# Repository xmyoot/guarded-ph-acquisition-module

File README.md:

# Guarded pH Acquisition Module

**Rev A · engineering prototype · CAD reviewed 21 October 2026 · unbuilt / hardware validation pending**

A 50 × 35 mm, two-layer pH analog front end for an external ESP32-S3 host. The design combines an LMP91200 electrode buffer, ADS112C04 16-bit delta-sigma ADC, REF3220 2.048 V reference, and a quiet 3.3 V supply with delayed reference enable.

*CAD rendering, not a photograph. The BNC connector is a drawing-derived visualization with threaded barrel, bayonet lugs and socket; small details are approximate, not vendor mechanical CAD.*

## Engineering focus

- Driven guards on both faces surround a 4.143 mm top-layer electrode trace with no vias or test-point stubs.
- Differential conversion at gain 2, external 2.048 V reference, and nominal 20 SPS single-shot mode; 31.25 µV per code. This is resolution, **not demonstrated accuracy**.
- Matched 1 kΩ input resistors and a 10 nF C0G differential capacitor; calculated pole 7.96 kHz.
- Supervisor-controlled reference startup, local test access, removable I²C pullups, and diagnostic/calibration firmware.
- Frozen project symbols and footprints; complete Gerber, drill, placement, and BOM outputs.
- Route cleanup reduced track segments from 352 to 257 and removed 8.203 mm of unnecessary copper while preserving locked analog geometry.

## Review status

Native KiCad 10.0.7 reports **0 ERC errors/warnings, 0 DRC violations, 0 unconnected pads, and 0 schematic-parity footprint errors**. A separate audit matches every native pad net and checks input geometry, copper exclusion, and via/paste separation. Generic analyzer findings and deliberate rule exceptions are explained in the [design review](docs/implementation/design_review.md).

The board has not been fabricated, assembled, powered, or tested. Leakage, noise, settling, startup, effective capacitor values, probe calibration, and interference remain hardware acceptance tests. The ≤0.01 pH electronics objective is an unproven target. There is no field ESD protection, onboard isolation, motor driver, battery system, radio, or cloud application.

## Files

| Deliverable | Location |
|---|---|
| Native KiCad project | [Soil_pH_AFE.kicad_pro](hardware/Soil_pH_AFE/Soil_pH_AFE.kicad_pro) |
| Schematic PDF | [schematic.pdf](output/review/schematic.pdf) |
| Fabrication package | [Rev A Gerber/drill ZIP](output/Soil_pH_AFE_RevA_fabrication.zip) |
| Fabrication and assembly instructions | [fabrication_notes.md](docs/implementation/fabrication_notes.md) |
| Orderable board BOM / host mating parts | [BOM.csv](output/assembly/BOM.csv) / [mating_parts.csv](output/assembly/mating_parts.csv) |
| Assembly drawing / placement | [assembly_top.pdf](output/assembly/assembly_top.pdf) / [placement_smd.csv](output/assembly/placement_smd.csv) |
| Firmware / bring-up | [Arduino sketch](firmware/SoilPH_Bringup/SoilPH_Bringup.ino) / [bringup.md](docs/implementation/bringup.md) |
| Review and decisions | [design_review.md](docs/implementation/design_review.md) / [decisions.md](docs/implementation/decisions.md) |
| Architecture and calculations | [Architecture](docs/architecture/01_architecture.md) / [calculations.json](docs/architecture/calculations.json) |
| Release hashes | [SHA256SUMS.txt](output/SHA256SUMS.txt) |
| Tools and reproducibility | [tools.md](docs/implementation/tools.md) |

## Scope and integration

This is an independent bench prototype based on an incomplete soil-instrument brief. Original Altium files and the promised replacement schematic were unavailable. The design therefore implements the requested analog chain on a separate board; it does not claim to preserve or reproduce the original product. Original client screenshots are retained locally and excluded from the public repository; the architecture contains the technical requirement summary.

Supply J2 with regulated 4.75–5.25 V and use 3.3 V open-drain I²C. J2: **1 = +5 V, 2 = ground, 3 = SDA, 4 = SCL, 5 = ground, 6 = reserved/unconnected**. Confirm pin 1 on the assembly drawing; do not infer it from viewing the cable end.

The insulated BNC shell is driven at approximately 1.024 V (`PH_VCM`); **it is not ground**. Use only a floating sample with no other conductive connection. Product integration requires a separately qualified isolated power and I²C interface, plus connector protection with a measured leakage budget. See [bring-up](docs/implementation/bringup.md) before applying power.

Phase 1 documents are retained as historical planning; final implementation decisions and BOM take precedence. Design/review used [kicad-happy](https://github.com/aklofas/kicad-happy) and routing used [KiCadRoutingTools](https://github.com/drandyhaas/KiCadRoutingTools), with manual protection of the high-impedance input and guard. Architecture was developed with Astra and implementation with 6.1 Sol; automated checks do not replace physical engineering qualification.

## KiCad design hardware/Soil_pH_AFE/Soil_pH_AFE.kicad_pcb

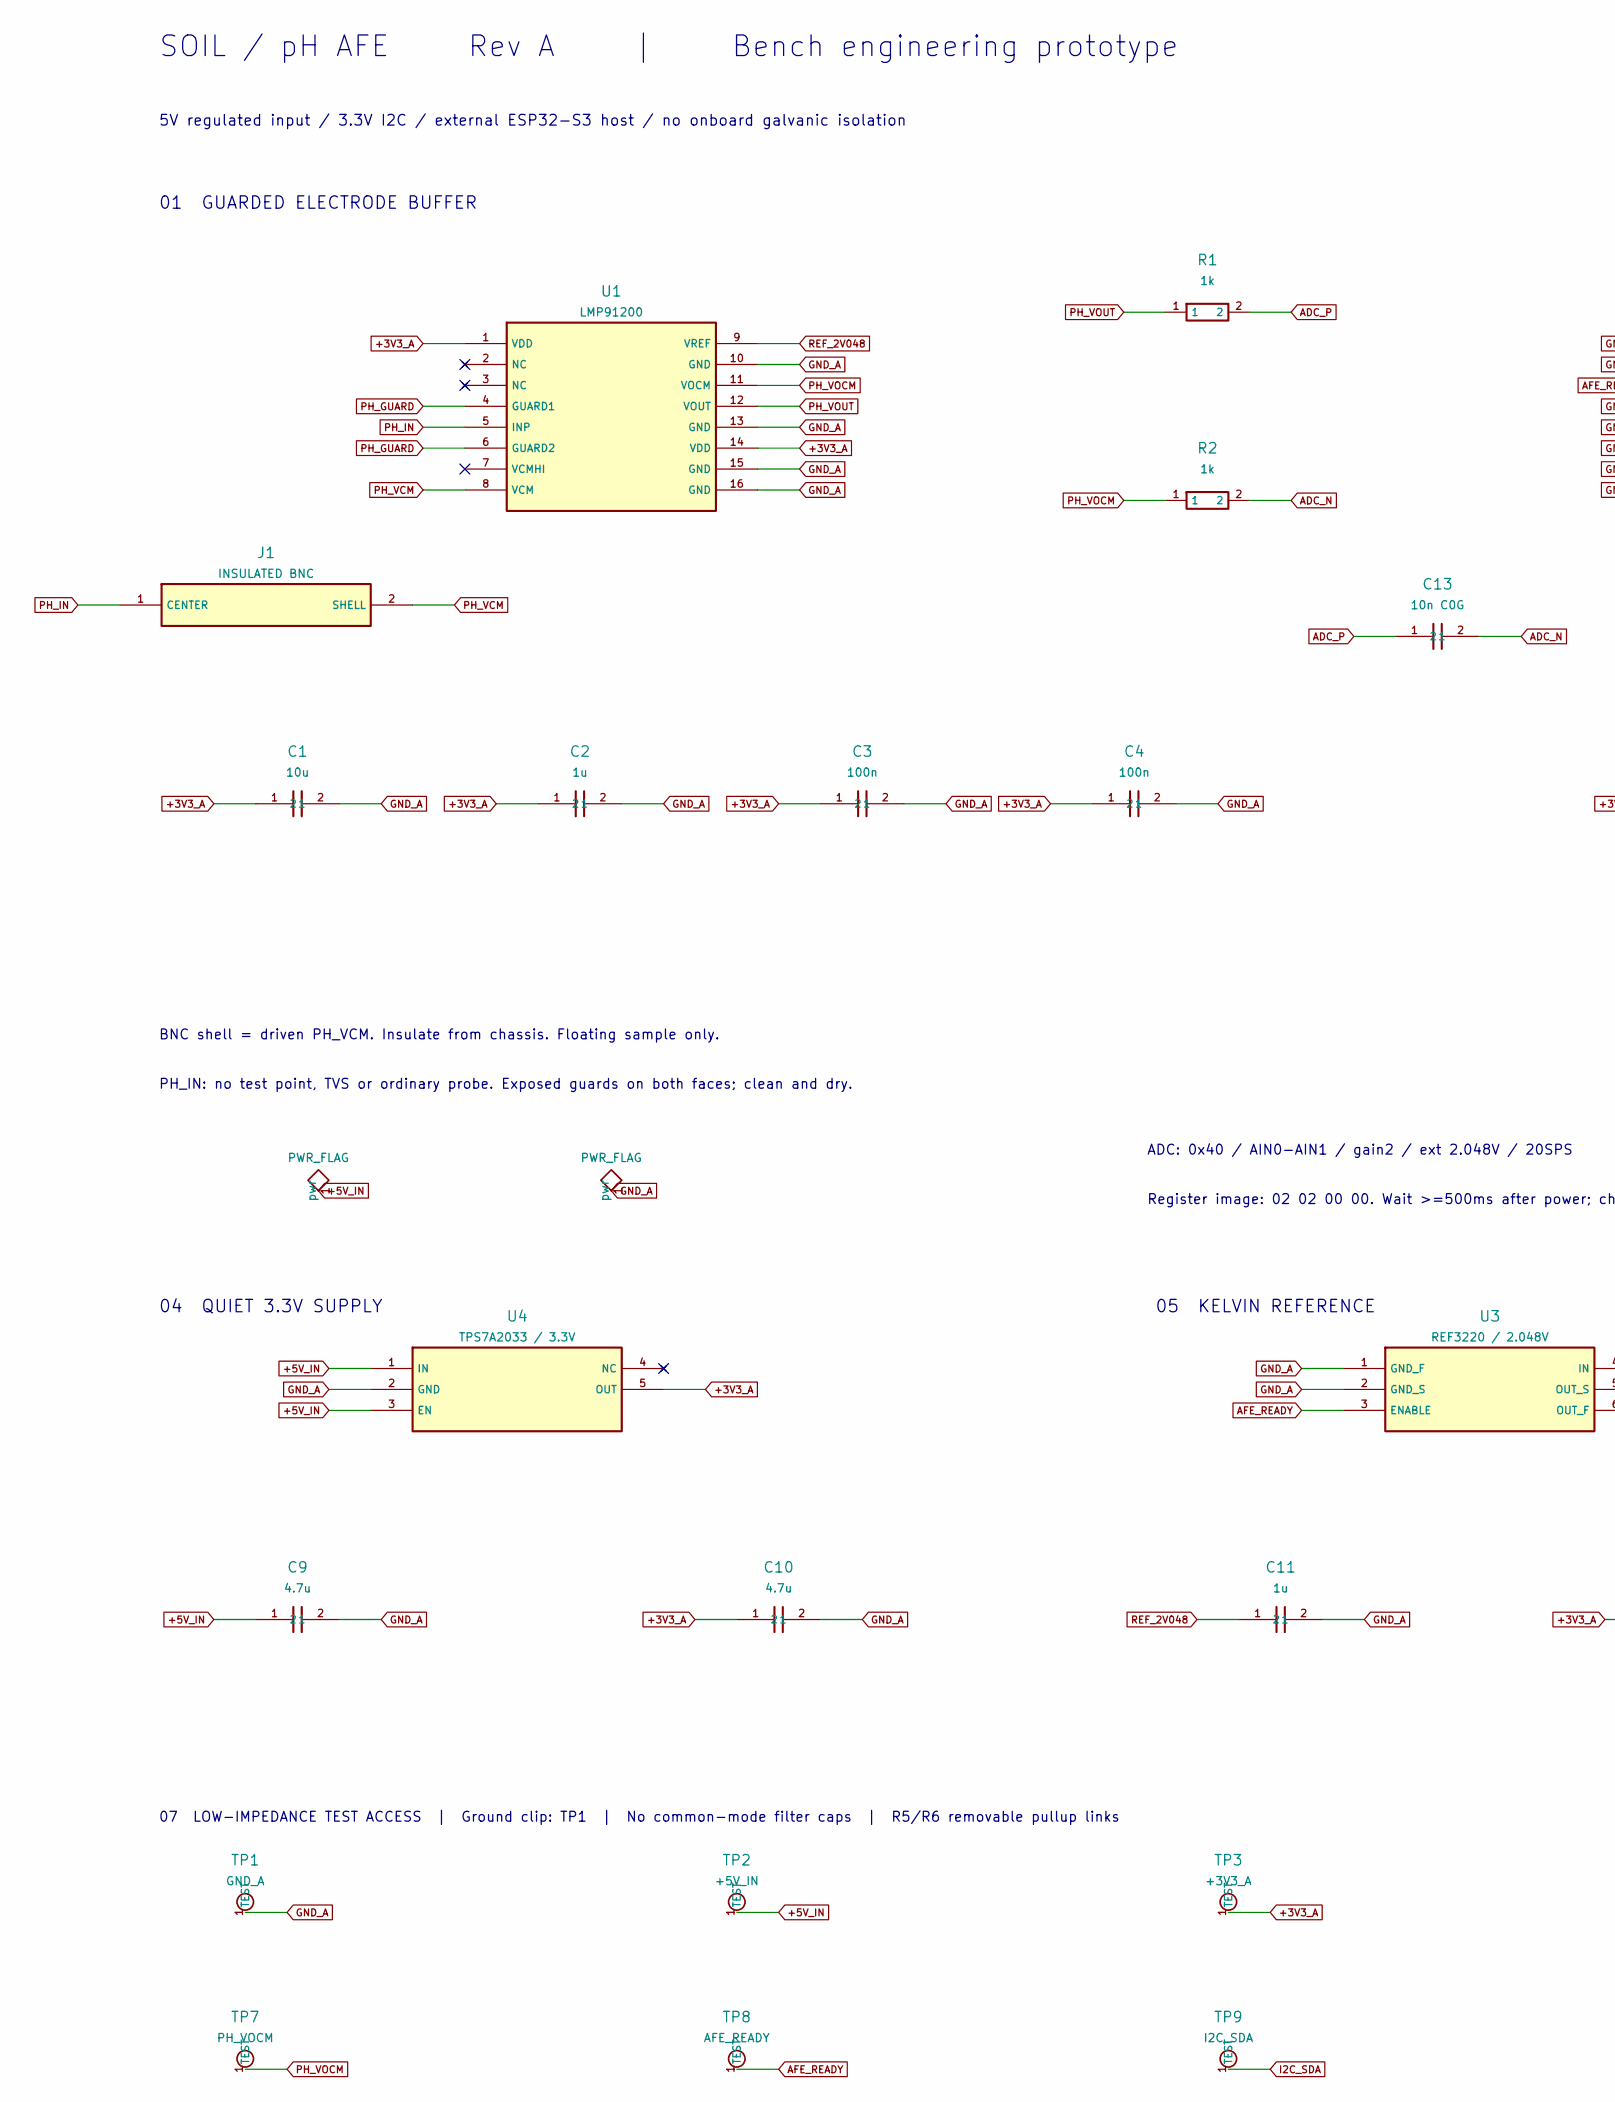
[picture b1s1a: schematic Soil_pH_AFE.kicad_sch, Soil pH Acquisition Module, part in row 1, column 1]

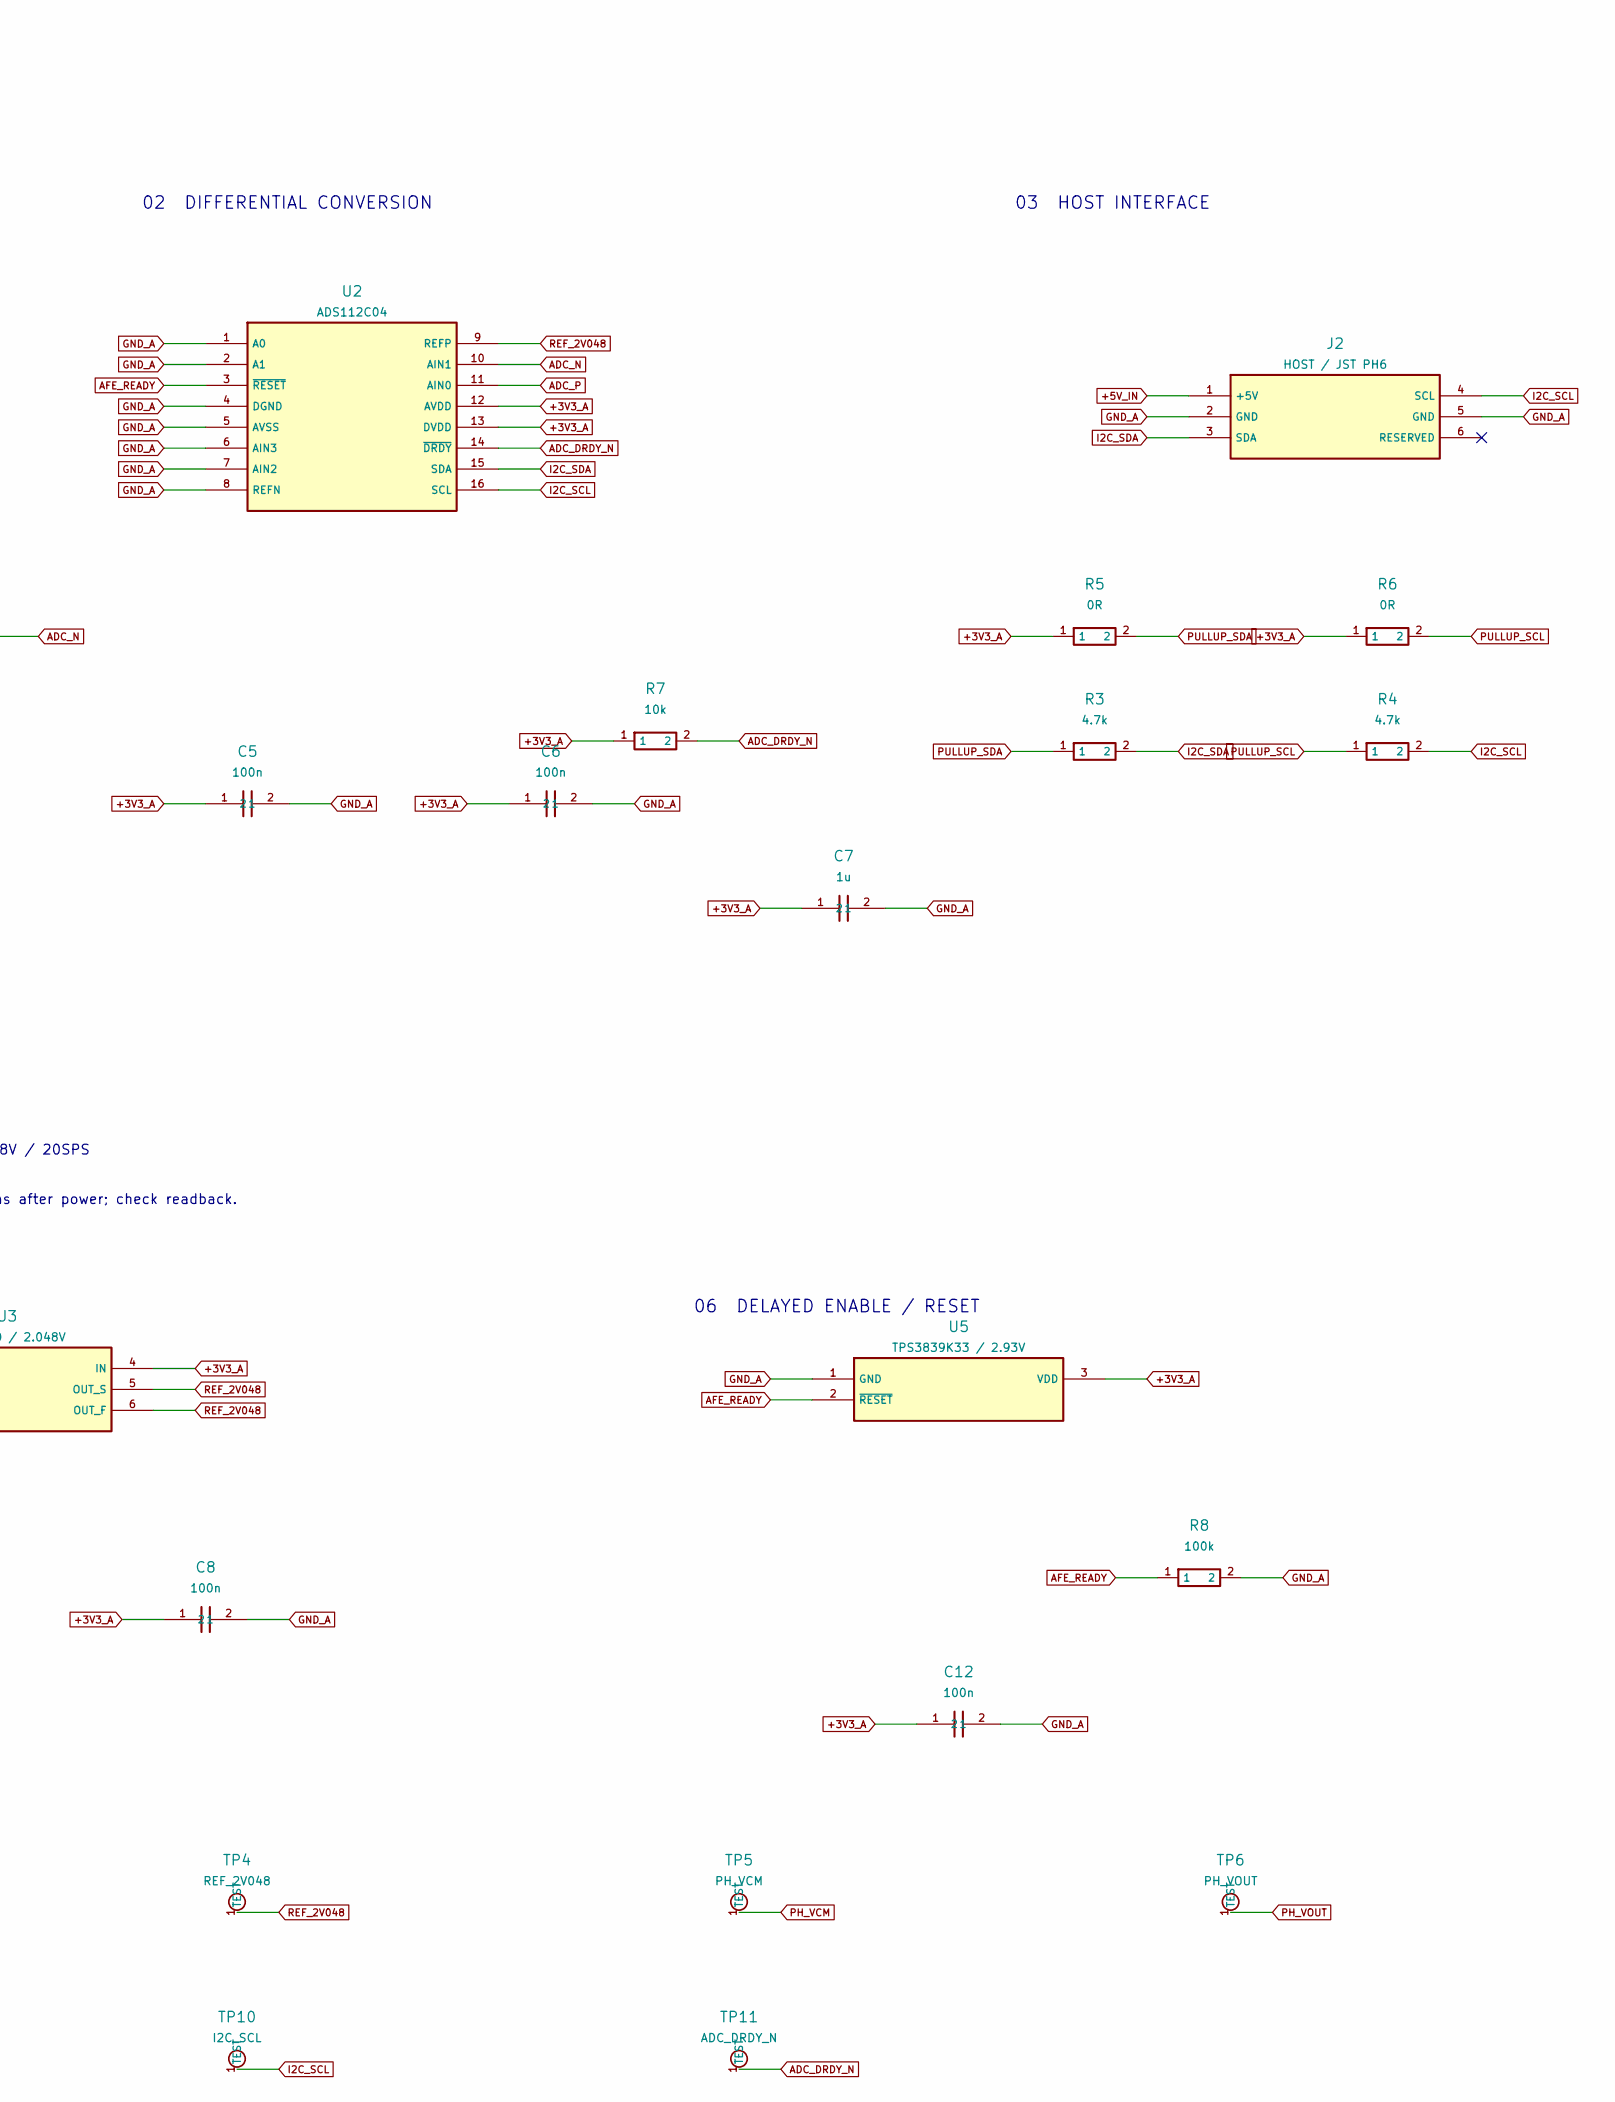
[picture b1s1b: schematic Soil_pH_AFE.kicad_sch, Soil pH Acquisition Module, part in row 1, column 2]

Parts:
C1: 10u; C_1206_3216Metric; MPN GRM31CR71C106KA12L
C2, C7, C11: 1u; C_0603_1608Metric; MPN GRM188R71C105KA12D
C3, C4, C5, C6, C8, C12: 100n; C_0603_1608Metric; MPN GRM188R71H104KA93D
C9, C10: 4.7u; C_0805_2012Metric; MPN GRM21BR71E475KA73L
C13: 10n C0G; C_0603_1608Metric; MPN GRM1885C1H103JA01D
J1: INSULATED BNC; BNC_031-5431-1010; MPN 031-5431-1010
J2: HOST / JST PH6; JST_PH_B6B-PH-K_1x06_P2.00mm_Vertical; MPN B6B-PH-K-S(LF)(SN)
R1, R2: 1k; R_0603_1608Metric; MPN TNPW06031K00BEEA
R3, R4: 4.7k; R_0603_1608Metric; MPN CRCW06034K70FKEA
R5, R6: 0R; R_0603_1608Metric; MPN CRCW06030000Z0EA
R7: 10k; R_0603_1608Metric; MPN CRCW060310K0FKEA
R8: 100k; R_0603_1608Metric; MPN CRCW0603100KFKEA
TP1: GND_A; TestPoint_Pad_D1.0mm; MPN PCB_FEATURE
TP2: +5V_IN; TestPoint_Pad_D1.0mm; MPN PCB_FEATURE
TP3: +3V3_A; TestPoint_Pad_D1.0mm; MPN PCB_FEATURE
TP4: REF_2V048; TestPoint_Pad_D1.0mm; MPN PCB_FEATURE
TP5: PH_VCM; TestPoint_Pad_D1.0mm; MPN PCB_FEATURE
TP6: PH_VOUT; TestPoint_Pad_D1.0mm; MPN PCB_FEATURE
TP7: PH_VOCM; TestPoint_Pad_D1.0mm; MPN PCB_FEATURE
TP8: AFE_READY; TestPoint_Pad_D1.0mm; MPN PCB_FEATURE
TP9: I2C_SDA; TestPoint_Pad_D1.0mm; MPN PCB_FEATURE
TP10: I2C_SCL; TestPoint_Pad_D1.0mm; MPN PCB_FEATURE
TP11: ADC_DRDY_N; TestPoint_Pad_D1.0mm; MPN PCB_FEATURE
U1: LMP91200; TSSOP-16_4.4x5mm_P0.65mm; MPN LMP91200MTX/NOPB
U2: ADS112C04; TSSOP-16_4.4x5mm_P0.65mm; MPN ADS112C04IPWR
U3: REF3220 / 2.048V; SOT-23-6; MPN REF3220AIDBVT
U4: TPS7A2033 / 3.3V; SOT-23-5; MPN TPS7A2033PDBVR
U5: TPS3839K33 / 2.93V; SOT-23; MPN TPS3839K33DBZT

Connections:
+3V3_A: C1.1, C2.1, C3.1, C4.1, C5.1, C6.1, C7.1, C8.1, C10.1, C12.1, R5.1, R6.1, R7.1, TP3.1 (TEST_1), U1.1 (VDD), U1.14 (VDD), U2.12 (AVDD), U2.13 (DVDD), U3.4 (IN), U4.5 (OUT), U5.3 (VDD)
+5V_IN: C9.1, J2.1 (+5V), TP2.1 (TEST_1), U4.1 (IN), U4.3 (EN)
ADC_DRDY_N: R7.2, TP11.1 (TEST_1), U2.14 (~DRDY)
ADC_N: C13.2, R2.2, U2.10 (AIN1)
ADC_P: C13.1, R1.2, U2.11 (AIN0)
AFE_READY: R8.1, TP8.1 (TEST_1), U2.3 (~RESET), U3.3 (ENABLE), U5.2 (~RESET)
GND_A: C1.2, C2.2, C3.2, C4.2, C5.2, C6.2, C7.2, C8.2, C9.2, C10.2, C11.2, C12.2, J2.2 (GND), J2.5 (GND), R8.2, TP1.1 (TEST_1), U1.10 (GND), U1.13 (GND), U1.15 (GND), U1.16 (GND), U2.1 (A0), U2.2 (A1), U2.4 (DGND), U2.5 (AVSS), U2.6 (AIN3), U2.7 (AIN2), U2.8 (REFN), U3.1 (GND_F), U3.2 (GND_S), U4.2 (GND), U5.1 (GND)
I2C_SCL: J2.4 (SCL), R4.2, TP10.1 (TEST_1), U2.16 (SCL)
I2C_SDA: J2.3 (SDA), R3.2, TP9.1 (TEST_1), U2.15 (SDA)
PH_GUARD: U1.4 (GUARD1), U1.6 (GUARD2)
PH_IN: J1.1 (CENTER), U1.5 (INP)
PH_VCM: J1.2 (SHELL), TP5.1 (TEST_1), U1.8 (VCM)
PH_VOCM: R2.1, TP7.1 (TEST_1), U1.11 (VOCM)
PH_VOUT: R1.1, TP6.1 (TEST_1), U1.12 (VOUT)
PULLUP_SCL: R4.1, R6.2
PULLUP_SDA: R3.1, R5.2
REF_2V048: C11.1, TP4.1 (TEST_1), U1.9 (VREF), U2.9 (REFP), U3.5 (OUT_S), U3.6 (OUT_F)

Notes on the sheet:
SOIL / pH AFE Rev A | Bench engineering prototype
5V regulated input / 3.3V I2C / external ESP32-S3 host / no onboard galvanic isolation
01 GUARDED ELECTRODE BUFFER
02 DIFFERENTIAL CONVERSION
03 HOST INTERFACE
BNC shell = driven PH_VCM. Insulate from chassis. Floating sample only.
PH_IN: no test point, TVS or ordinary probe. Exposed guards on both faces; clean and dry.
04 QUIET 3.3V SUPPLY
05 KELVIN REFERENCE
06 DELAYED ENABLE / RESET
07 LOW-IMPEDANCE TEST ACCESS | Ground clip: TP1 | No common-mode filter caps | R5/R6 removable pullup links
ADC: 0x40 / AIN0-AIN1 / gain2 / ext 2.048V / 20SPS
Register image: 02 02 00 00. Wait >=500ms after power; check readback.

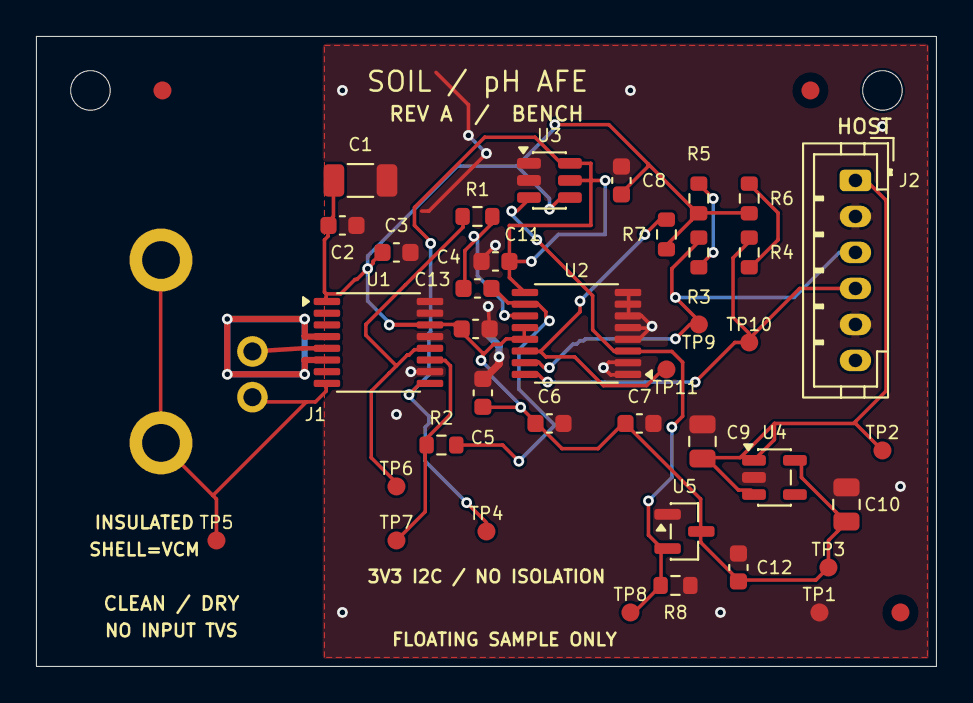
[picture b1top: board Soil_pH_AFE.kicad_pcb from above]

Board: 2 copper layers, 50.0 x 35.0 mm, 44 parts (0 on the bottom side), 17 nets.

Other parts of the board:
FID1, FID2, FID3: OPTICAL; Fiducial_1mm_Mask2mm
H1, H2: M2 NPTH; MountingHole_2.2mm_M2

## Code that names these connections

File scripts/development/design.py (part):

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TI=lambda n:'https://www.ti.com/lit/ds/symlink/'+n.lower()+'.pdf'
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add('U3','REF3220 / 2.048V','Package_TO_SOT_SMD:SOT-23-6','REF3220AIDBVT',['GND_A','GND_A','AFE_READY','+3V3_A','REF_2V048','REF_2V048'],[128.5,108],[187,183],ds=TI('ref3220'),pins=[('GND_F','power_in'),('GND_S','input'),('ENABLE','input'),('IN','power_in'),('OUT_S','input'),('OUT_F','power_out')])
add('U4','TPS7A2033 / 3.3V','Package_TO_SOT_SMD:SOT-23-5','TPS7A2033PDBVR',['+5V_IN','GND_A','+5V_IN',None,'+3V3_A'],[141,124.5],[68,183],ds=TI('tps7a20'),pins=[('IN','power_in'),('GND','power_in'),('EN','input'),('NC','no_connect'),('OUT','power_out')])
add('U5','TPS3839K33 / 2.93V','Package_TO_SOT_SMD:SOT-23','TPS3839K33DBZT',['GND_A','AFE_READY','+3V3_A'],[136,127.5],[302,183],ds=TI('tps3839'),pins=[('GND','power_in'),('~{RESET}','output'),('VDD','power_in')])
add('J1','INSULATED BNC','Soil_pH:BNC_031-5431-1010','031-5431-1010',['PH_IN','PH_VCM'],[112,117.5],[38,88],rot=90,ds='https://www.amphenolrf.com/en-us/assets/file/4065788069/',pins=[('CENTER','passive'),('SHELL','passive')])
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def res(r,v,n,xy,sch,mpn=None,rot=0):
 add(r,v,'Resistor_SMD:R_0603_1608Metric',mpn or {'1k':'TNPW06031K00BEEA','4.7k':'CRCW06034K70FKEA','10k':'CRCW060310K0FKEA','100k':'CRCW0603100KFKEA','0R':'CRCW06030000Z0EA'}[v],n,xy,sch,rot)
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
